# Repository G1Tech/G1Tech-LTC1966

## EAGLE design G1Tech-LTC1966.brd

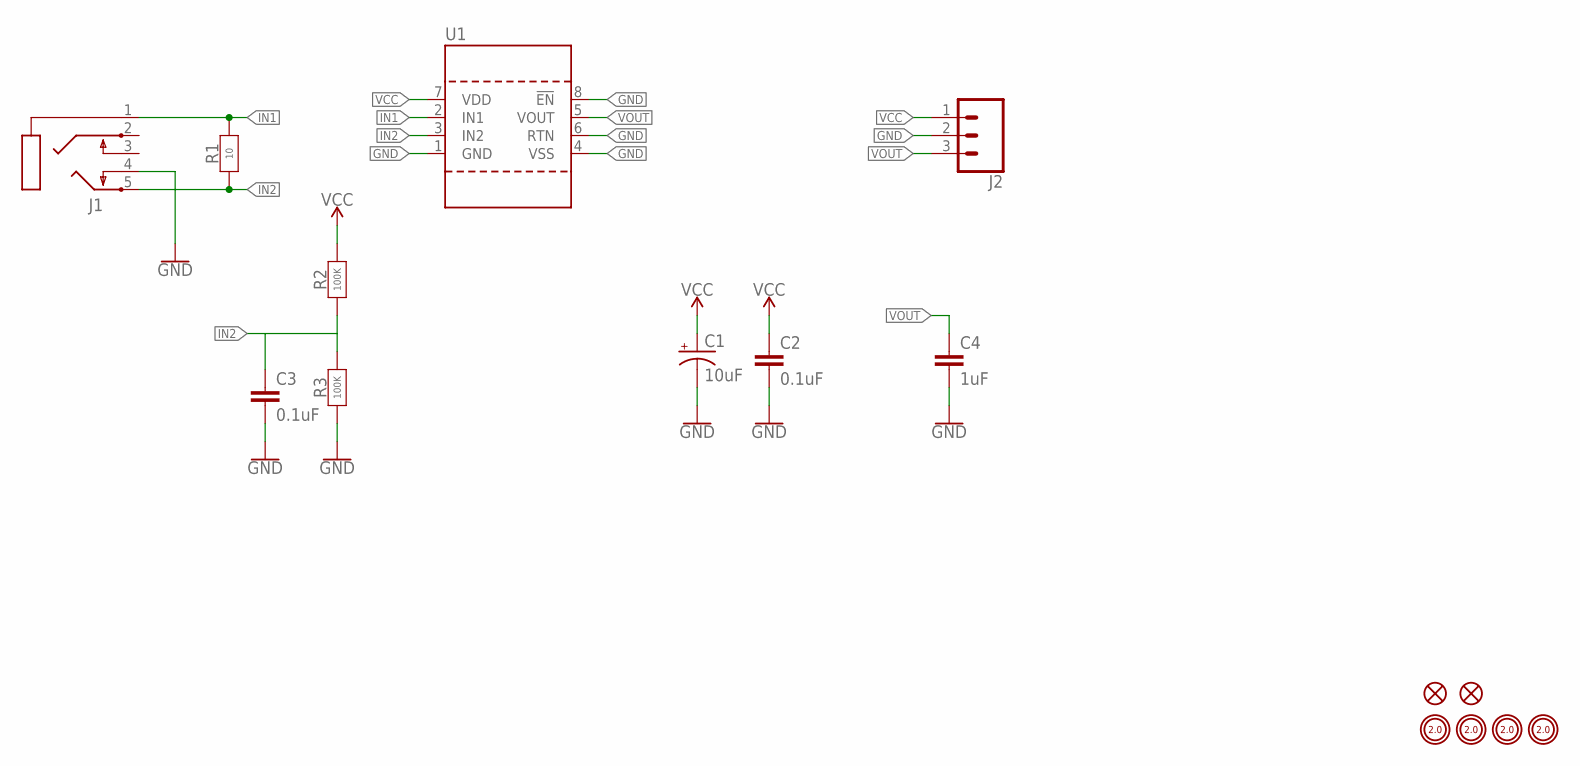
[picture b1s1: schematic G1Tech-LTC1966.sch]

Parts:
C1: 10uF; TYPE-A
C2, C3: 0.1uF; C0603
C4: 1uF; C0603
FD1, FD2: FIDUCIAL-1X2
H1, H2, H3, H4: MOUNTINGHOLE-PLATED-2.0
J1: PJ-3126-5A
J2: CONN-1X3; 1X03_NO_SILK
R1: 10; YAGEO-R0603
R2, R3: 100K; YAGEO-R0603
U1: LTC1966; MS8

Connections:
GND: C1.C, C2.2, C3.2, C4.2, J1.4, J2.2, R3.1, U1.1 (GND), U1.4 (VSS), U1.6 (RTN), U1.8 (!EN)
IN1: J1.1, R1.2, U1.2 (IN1)
IN2: C3.1, J1.5, R1.1, R2.1, R3.2, U1.3 (IN2)
VCC: C1.A, C2.1, J2.1, R2.2, U1.7 (VDD)
VOUT: C4.1, J2.3, U1.5 (VOUT)

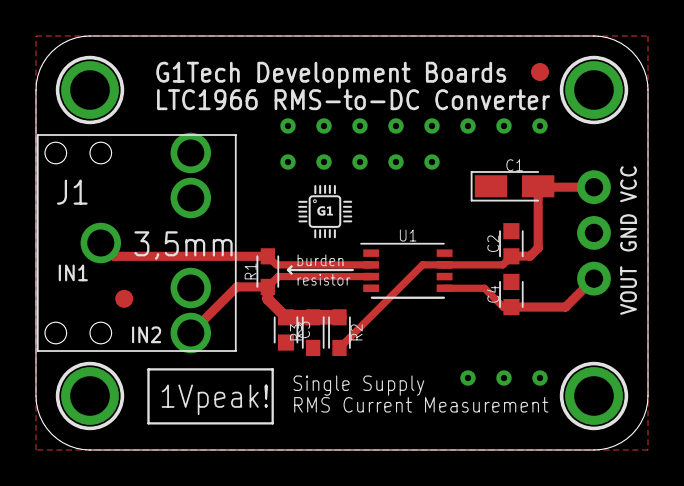
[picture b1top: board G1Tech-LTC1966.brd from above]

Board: 2 copper layers, 34.0 x 23.0 mm, 18 parts (1 on the bottom side), 5 nets.

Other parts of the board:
U$1: LOGO-G1TECH-5MM
U$2: LOGO-G1TECH-3MM
